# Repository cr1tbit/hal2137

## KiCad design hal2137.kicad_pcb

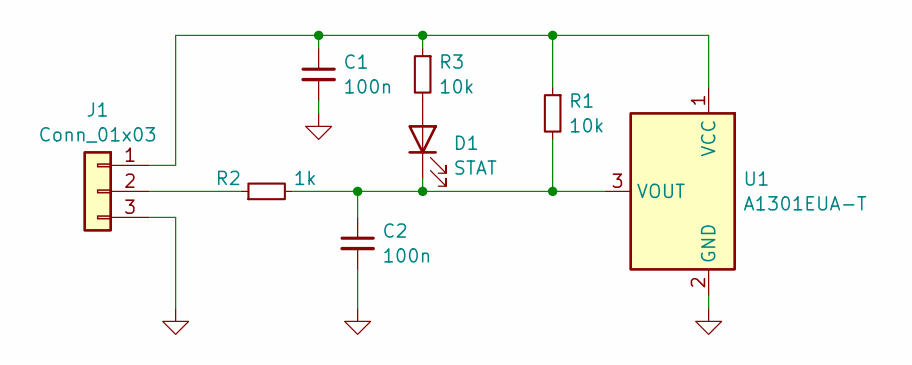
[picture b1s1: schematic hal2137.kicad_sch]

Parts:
C1, C2: 100n; C_0805_2012Metric_Pad1.18x1.45mm_HandSolder
D1: STAT; LED_0603_1608Metric_Pad1.05x0.95mm_HandSolder
J1: Conn_01x03; PinSocket_1x03_P2.54mm_Vertical
R1, R3: 10k; R_0805_2012Metric_Pad1.20x1.40mm_HandSolder
R2: 1k; R_0805_2012Metric_Pad1.20x1.40mm_HandSolder
U1: A1301EUA-T; Diodes_SIP-3_4.1x1.5mm_P2.65mm

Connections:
GND: C1.2, C2.2, J1.3, U1.2 (GND)
unnamed: D1.2 (A), R3.2
unnamed: C2.1, D1.1 (K), R1.2, R2.2, U1.3 (VOUT)
unnamed: C1.1, J1.1, R1.1, R3.1, U1.1 (VCC)
unnamed: J1.2, R2.1

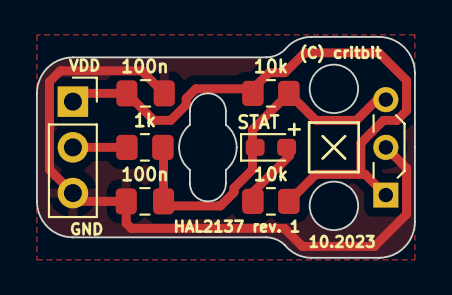
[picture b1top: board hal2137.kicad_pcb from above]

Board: 2 copper layers, 21.0 x 12.3 mm, 8 parts (0 on the bottom side), 5 nets.

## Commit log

2023-10-21 hallo haha
